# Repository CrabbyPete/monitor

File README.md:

# crib

## Getting started

To make it easy for you to get started with GitLab, here's a list of recommended next steps.

Already a pro? Just edit this README.md and make it your own. Want to make it easy? [Use the template at the bottom](#editing-this-readme)!

## Add your files

- [ ] [Create](https://docs.gitlab.com/ee/user/project/repository/web_editor.html#create-a-file) or [upload](https://docs.gitlab.com/ee/user/project/repository/web_editor.html#upload-a-file) files
- [ ] [Add files using the command line](https://docs.gitlab.com/ee/gitlab-basics/add-file.html#add-a-file-using-the-command-line) or push an existing Git repository with the following command:

```
cd existing_repo
git remote add origin https://gitlab.com/CrabbyPete/crib.git
git branch -M main
git push -uf origin main
```

## Integrate with your tools

- [ ] [Set up project integrations](https://gitlab.com/CrabbyPete/crib/-/settings/integrations)

## Collaborate with your team

- [ ] [Invite team members and collaborators](https://docs.gitlab.com/ee/user/project/members/)
- [ ] [Create a new merge request](https://docs.gitlab.com/ee/user/project/merge_requests/creating_merge_requests.html)
- [ ] [Automatically close issues from merge requests](https://docs.gitlab.com/ee/user/project/issues/managing_issues.html#closing-issues-automatically)
- [ ] [Enable merge request approvals](https://docs.gitlab.com/ee/user/project/merge_requests/approvals/)
- [ ] [Set auto-merge](https://docs.gitlab.com/ee/user/project/merge_requests/merge_when_pipeline_succeeds.html)

## Test and Deploy

Use the built-in continuous integration in GitLab.

- [ ] [Get started with GitLab CI/CD](https://docs.gitlab.com/ee/ci/quick_start/index.html)
- [ ] [Analyze your code for known vulnerabilities with Static Application Security Testing (SAST)](https://docs.gitlab.com/ee/user/application_security/sast/)
- [ ] [Deploy to Kubernetes, Amazon EC2, or Amazon ECS using Auto Deploy](https://docs.gitlab.com/ee/topics/autodevops/requirements.html)
- [ ] [Use pull-based deployments for improved Kubernetes management](https://docs.gitlab.com/ee/user/clusters/agent/)
- [ ] [Set up protected environments](https://docs.gitlab.com/ee/ci/environments/protected_environments.html)

***

# Editing this README

When you're ready to make this README your own, just edit this file and use the handy template below (or feel free to structure it however you want - this is just a starting point!). Thanks to [makeareadme.com](https://www.makeareadme.com/) for this template.

## Suggestions for a good README

Every project is different, so consider which of these sections apply to yours. The sections used in the template are suggestions for most open source projects. Also keep in mind that while a README can be too long and detailed, too long is better than too short. If you think your README is too long, consider utilizing another form of documentation rather than cutting out information.

## Name
Choose a self-explaining name for your project.

## Description
Let people know what your project can do specifically. Provide context and add a link to any reference visitors might be unfamiliar with. A list of Features or a Background subsection can also be added here. If there are alternatives to your project, this is a good place to list differentiating factors.

## Badges
On some READMEs, you may see small images that convey metadata, such as whether or not all the tests are passing for the project. You can use Shields to add some to your README. Many services also have instructions for adding a badge.

## Visuals
Depending on what you are making, it can be a good idea to include screenshots or even a video (you'll frequently see GIFs rather than actual videos). Tools like ttygif can help, but check out Asciinema for a more sophisticated method.

## Installation
Within a particular ecosystem, there may be a common way of installing things, such as using Yarn, NuGet, or Homebrew. However, consider the possibility that whoever is reading your README is a novice and would like more guidance. Listing specific steps helps remove ambiguity and gets people to using your project as quickly as possible. If it only runs in a specific context like a particular programming language version or operating system or has dependencies that have to be installed manually, also add a Requirements subsection.

## Usage
Use examples liberally, and show the expected output if you can. It's helpful to have inline the smallest example of usage that you can demonstrate, while providing links to more sophisticated examples if they are too long to reasonably include in the README.

## Support
Tell people where they can go to for help. It can be any combination of an issue tracker, a chat room, an email address, etc.

## Roadmap
If you have ideas for releases in the future, it is a good idea to list them in the README.

## Contributing
State if you are open to contributions and what your requirements are for accepting them.

For people who want to make changes to your project, it's helpful to have some documentation on how to get started. Perhaps there is a script that they should run or some environment variables that they need to set. Make these steps explicit. These instructions could also be useful to your future self.

You can also document commands to lint the code or run tests. These steps help to ensure high code quality and reduce the likelihood that the changes inadvertently break something. Having instructions for running tests is especially helpful if it requires external setup, such as starting a Selenium server for testing in a browser.

## Authors and acknowledgment
Show your appreciation to those who have contributed to the project.

## License
For open source projects, say how it is licensed.

## Project status
If you have run out of energy or time for your project, put a note at the top of the README saying that development has slowed down or stopped completely. Someone may choose to fork your project or volunteer to step in as a maintainer or owner, allowing your project to keep going. You can also make an explicit request for maintainers.

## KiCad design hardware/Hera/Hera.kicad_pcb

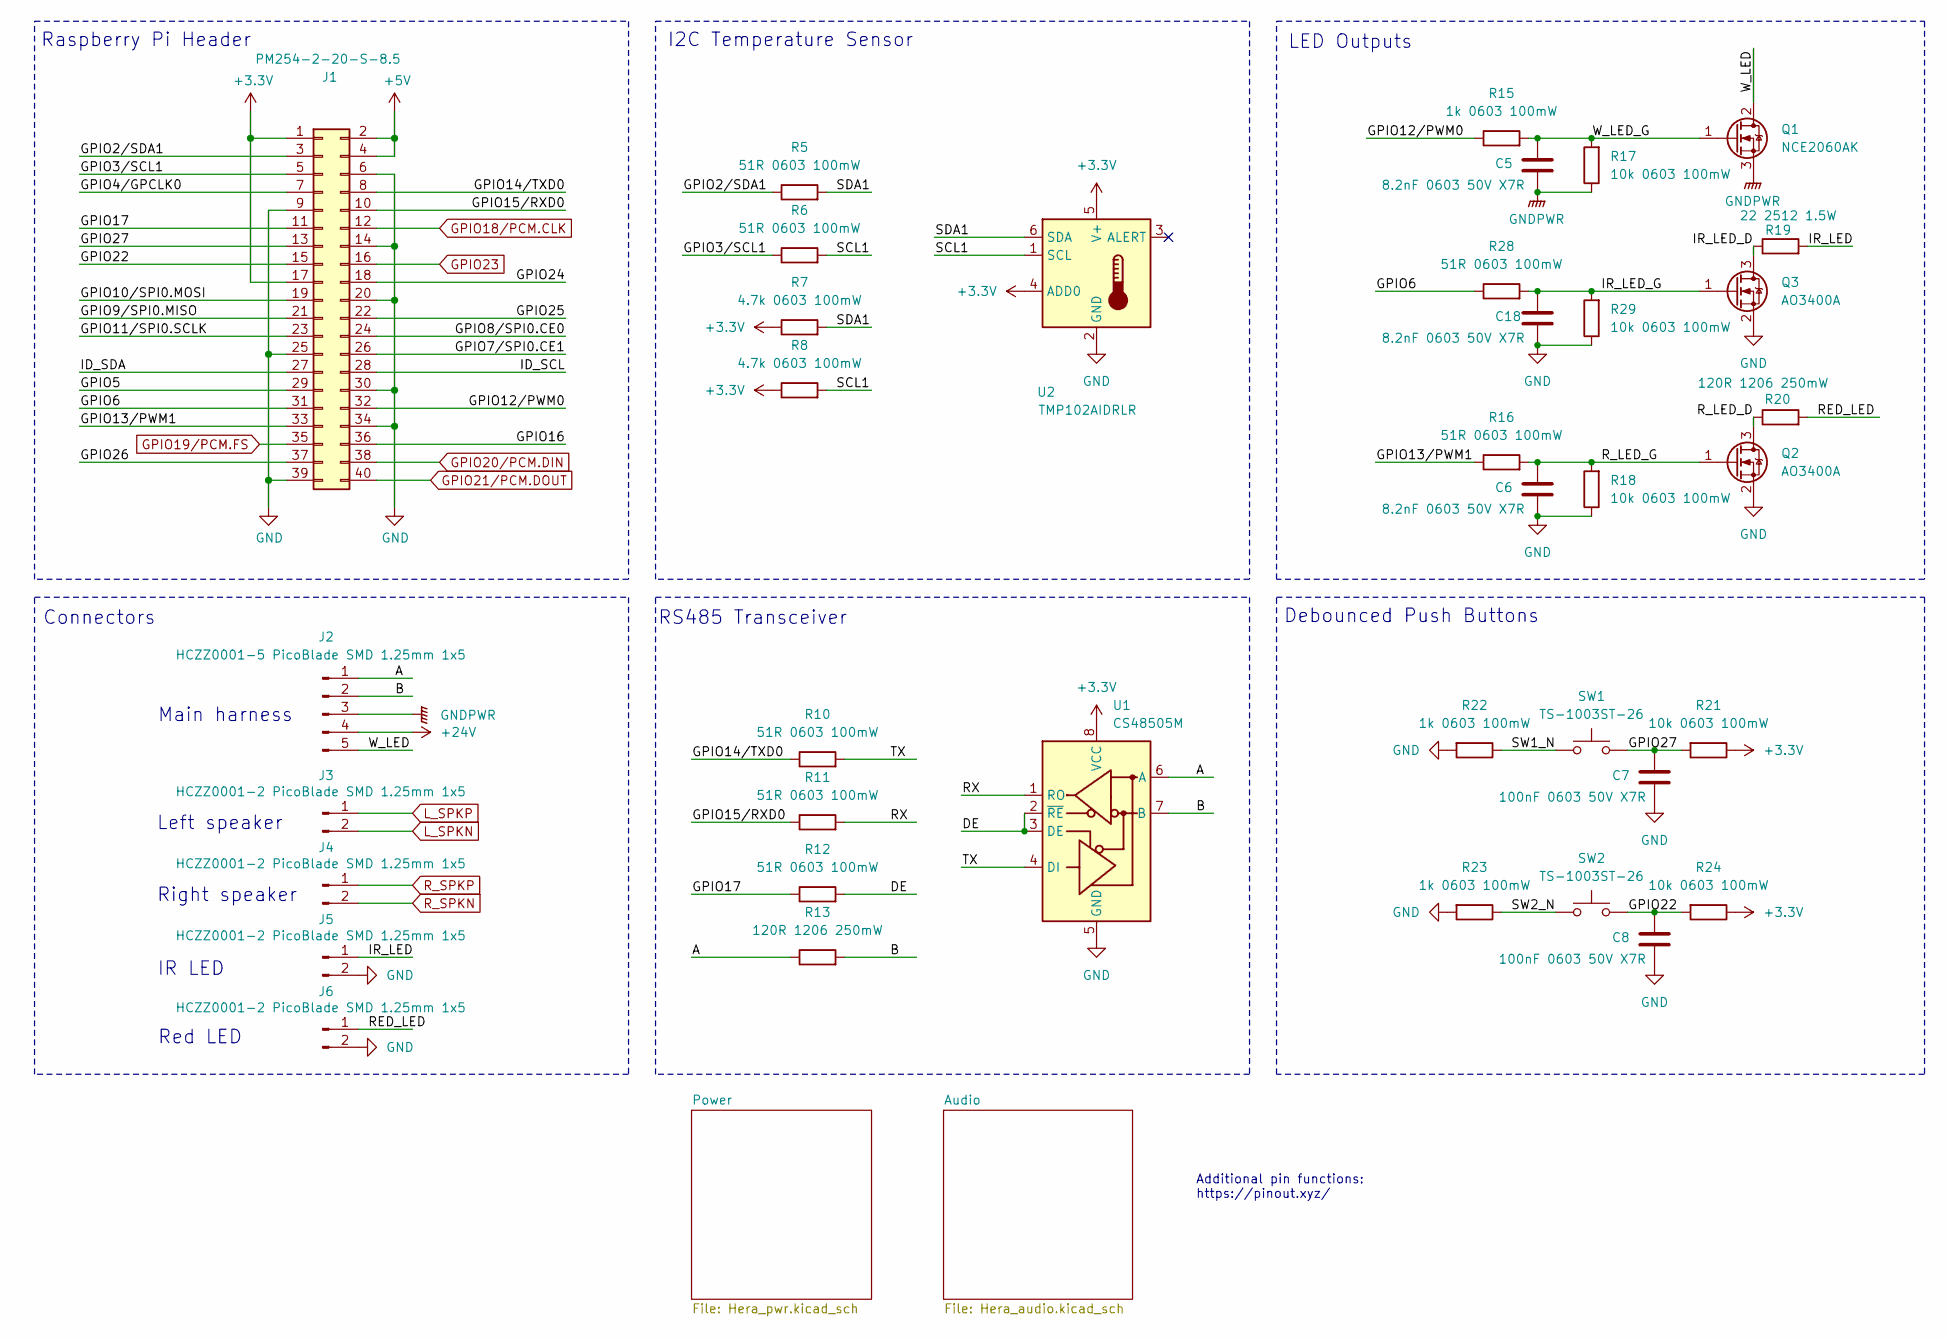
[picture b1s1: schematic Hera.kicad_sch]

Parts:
C5, C6, C18: 8.2nF 0603 50V X7R; C_0603_1608Metric
C7, C8: 100nF 0603 50V X7R; C_0603_1608Metric
J1: PM254-2-20-S-8.5; PinSocket_2x20_P2.54mm_Vertical_SMD
J2: HCZZ0001-5 PicoBlade SMD 1.25mm 1x5; Molex_PicoBlade_53261-0571_1x05-1MP_P1.25mm_Horizontal
J3, J4, J5, J6: HCZZ0001-2 PicoBlade SMD 1.25mm 1x5; Molex_PicoBlade_53261-0271_1x02-1MP_P1.25mm_Horizontal
Q1: NCE2060AK; TO-252-2
Q2, Q3: AO3400A; SOT-23
R5, R6, R10, R11, R12, R16, R28: 51R 0603 100mW; R_0603_1608Metric
R7, R8: 4.7k 0603 100mW; R_0603_1608Metric
R13, R20: 120R 1206 250mW; R_1206_3216Metric
R15, R22, R23: 1k 0603 100mW; R_0603_1608Metric
R17, R18, R21, R24, R29: 10k 0603 100mW; R_0603_1608Metric
R19: 22 2512 1.5W; R_2512_6332Metric
SW1, SW2: TS-1003ST-26; SW_Push_1P1T_NO_CK_PTS125Sx43PSMTR
U1: CS48505M; MSOP-8_3x3mm_P0.65mm
U2: TMP102AIDRLR; SOT-563

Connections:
+3.3V: J1.1, J1.17, R7.1, R8.1, R21.1, R24.1, U1.8 (VCC), U2.4 (ADD0), U2.5 (V+); also elsewhere on the board
+5V: J1.2, J1.4; also elsewhere on the board
+24V: J2.4; also elsewhere on the board
/A: J2.1, R13.1, U1.6 (A)
/B: J2.2, R13.2, U1.7 (B)
/DE: R12.2, U1.2 (~RE), U1.3 (DE)
/GPIO2/SDA1: J1.3, R5.1
/GPIO3/SCL1: J1.5, R6.1
/GPIO4/GPCLK0: J1.7
/GPIO5: J1.29
/GPIO6: J1.31, R28.1
/GPIO7/SPI0.CE1: J1.26
/GPIO8/SPI0.CE0: J1.24
/GPIO9/SPI0.MISO: J1.21
/GPIO10/SPI0.MOSI: J1.19
/GPIO11/SPI0.SCLK: J1.23
/GPIO12/PWM0: J1.32, R15.1
/GPIO13/PWM1: J1.33, R16.1
/GPIO14/TXD0: J1.8, R10.1
/GPIO15/RXD0: J1.10, R11.1
/GPIO16: J1.36
/GPIO17: J1.11, R12.1
/GPIO22: C8.1, J1.15, R24.2, SW2.2
/GPIO24: J1.18
/GPIO25: J1.22
/GPIO26: J1.37
/GPIO27: C7.1, J1.13, R21.2, SW1.2
/ID_SCL: J1.28
/ID_SDA: J1.27
/IR_LED: J5.1, R19.2
/IR_LED_D: Q3.3 (D), R19.1
/IR_LED_G: C18.1, Q3.1 (G), R28.2, R29.2
/RED_LED: J6.1, R20.2
/RX: R11.2, U1.1 (RO)
/R_LED_D: Q2.3 (D), R20.1
/R_LED_G: C6.1, Q2.1 (G), R16.2, R18.2
/SCL1: R6.2, R8.2, U2.1 (SCL)
/SDA1: R5.2, R7.2, U2.6 (SDA)
/SW1_N: R22.1, SW1.1
/SW2_N: R23.1, SW2.1
/TX: R10.2, U1.4 (DI)
/W_LED: J2.5, Q1.2 (D)
/W_LED_G: C5.1, Q1.1 (G), R15.2, R17.2
GND: C6.2, C7.2, C8.2, C18.2, J1.6, J1.9, J1.14, J1.20, J1.25, J1.30, J1.34, J1.39, J5.2, J6.2, Q2.2 (S), Q3.2 (S), R18.1, R22.2, R23.2, R29.1, U1.5 (GND), U2.2 (GND); also elsewhere on the board
GNDPWR: C5.2, J2.3, Q1.3 (S), R17.1; also elsewhere on the board
GPIO18/PCM.CLK: J1.12; also elsewhere on the board
GPIO19/PCM.FS: J1.35; also elsewhere on the board
GPIO20/PCM.DIN: J1.38; also elsewhere on the board
GPIO21/PCM.DOUT: J1.40; also elsewhere on the board
GPIO23: J1.16; also elsewhere on the board
L_SPKN: J3.2; also elsewhere on the board
L_SPKP: J3.1; also elsewhere on the board
R_SPKN: J4.2; also elsewhere on the board
R_SPKP: J4.1; also elsewhere on the board

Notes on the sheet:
Red LED
RS485 Transceiver
Main harness
IR LED
Right speaker
Left speaker
LED Outputs
Raspberry Pi Header
Connectors
I2C Temperature Sensor
Debounced Push Buttons
Additional pin functions: https://pinout.xyz/

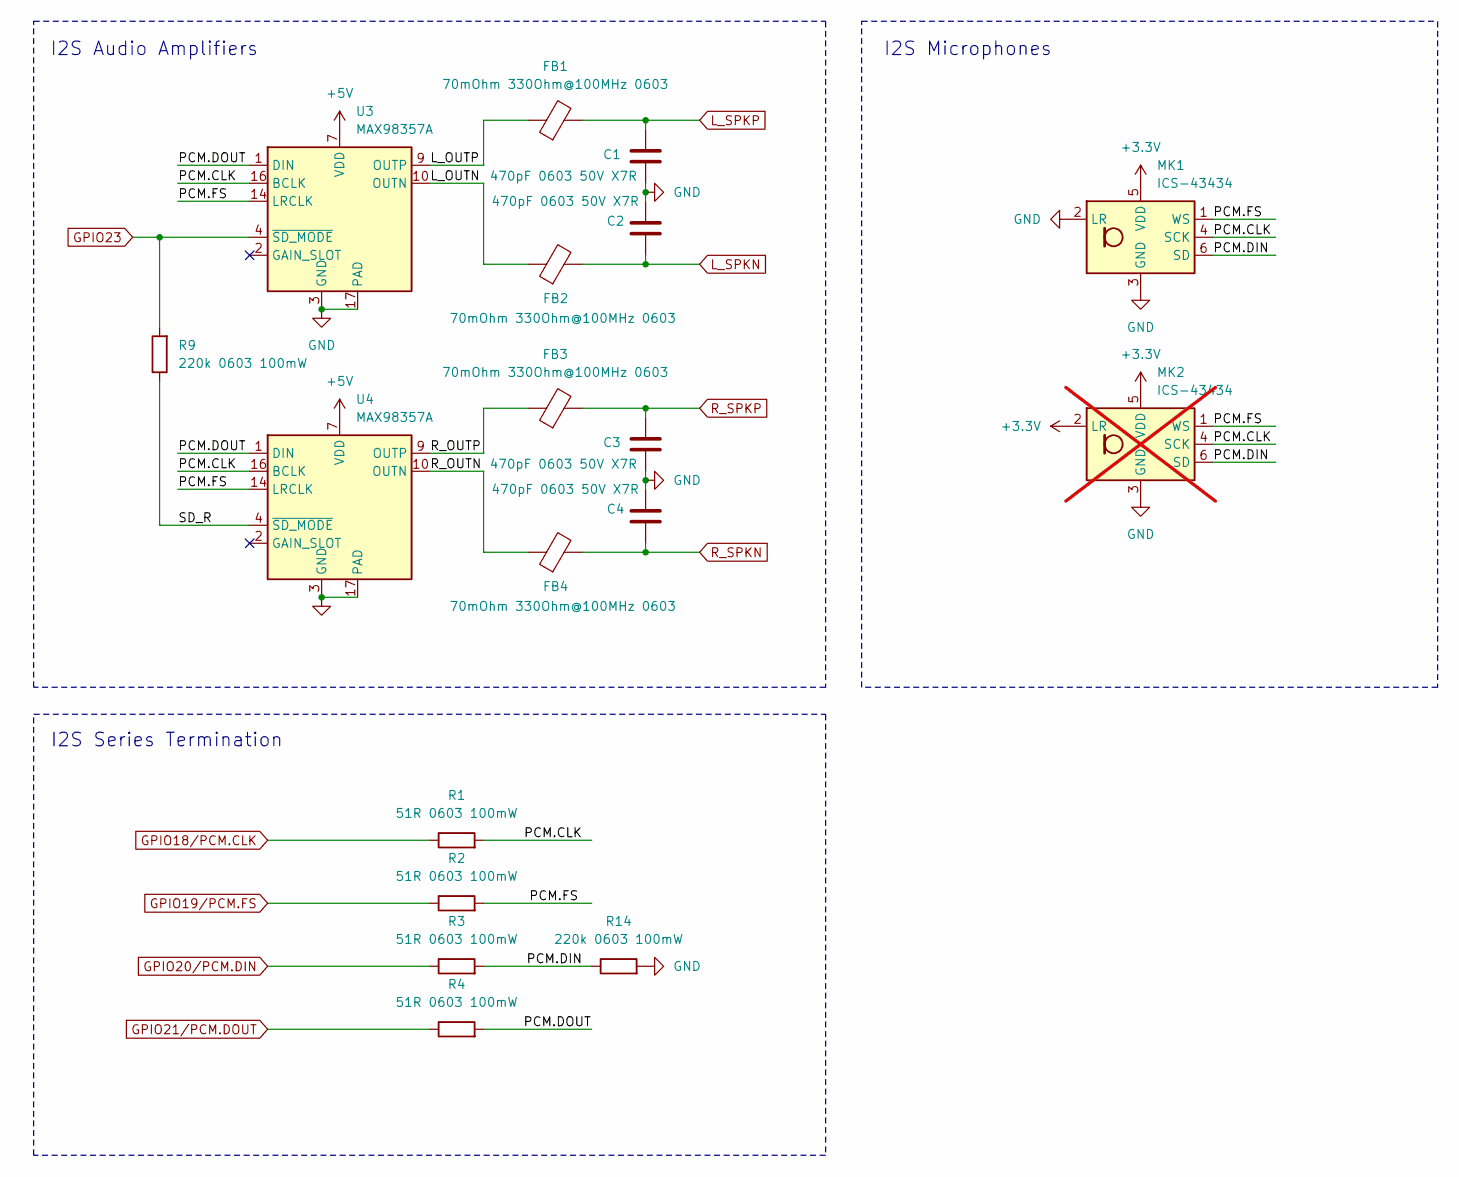
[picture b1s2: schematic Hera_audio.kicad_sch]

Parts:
C1, C2, C3, C4: 470pF 0603 50V X7R; C_0603_1608Metric
FB1, FB2, FB3, FB4: 70mOhm 330Ohm@100MHz 0603; L_0603_1608Metric
MK1: ICS-43434; InvenSense_ICS-43434-6_3.5x2.65mm
MK2: ICS-43434; InvenSense_ICS-43434-6_3.5x2.65mm; not fitted
R1, R2, R3, R4: 51R 0603 100mW; R_0603_1608Metric
R9, R14: 220k 0603 100mW; R_0603_1608Metric
U3, U4: MAX98357A; TQFN-16-1EP_3x3mm_P0.5mm_EP1.23x1.23mm

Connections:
+3.3V: MK1.5 (VDD), MK2.2 (LR), MK2.5 (VDD); also elsewhere on the board
+5V: U3.7 (VDD), U3.8 (VDD), U4.7 (VDD), U4.8 (VDD); also elsewhere on the board
/Audio/L_OUTN: FB2.1, U3.10 (OUTN)
/Audio/L_OUTP: FB1.1, U3.9 (OUTP)
/Audio/PCM.CLK: MK1.4 (SCK), MK2.4 (SCK), R1.2, U3.16 (BCLK), U4.16 (BCLK)
/Audio/PCM.DIN: MK1.6 (SD), MK2.6 (SD), R3.2, R14.1
/Audio/PCM.DOUT: R4.2, U3.1 (DIN), U4.1 (DIN)
/Audio/PCM.FS: MK1.1 (WS), MK2.1 (WS), R2.2, U3.14 (LRCLK), U4.14 (LRCLK)
/Audio/R_OUTN: FB4.1, U4.10 (OUTN)
/Audio/R_OUTP: FB3.1, U4.9 (OUTP)
/Audio/SD_R: R9.1, U4.4 (~SD_MODE)
GND: C1.2, C2.1, C3.2, C4.1, MK1.2 (LR), MK1.3 (GND), MK2.3 (GND), R14.2, U3.3 (GND), U3.11 (GND), U3.15 (GND), U3.17 (PAD), U4.3 (GND), U4.11 (GND), U4.15 (GND), U4.17 (PAD); also elsewhere on the board
GPIO18/PCM.CLK: R1.1; also elsewhere on the board
GPIO19/PCM.FS: R2.1; also elsewhere on the board
GPIO20/PCM.DIN: R3.1; also elsewhere on the board
GPIO21/PCM.DOUT: R4.1; also elsewhere on the board
GPIO23: R9.2, U3.4 (~SD_MODE); also elsewhere on the board
L_SPKN: C2.2, FB2.2; also elsewhere on the board
L_SPKP: C1.1, FB1.2; also elsewhere on the board
R_SPKN: C4.2, FB4.2; also elsewhere on the board
R_SPKP: C3.1, FB3.2; also elsewhere on the board

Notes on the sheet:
I2S Audio Amplifiers
I2S Microphones
I2S Series Termination

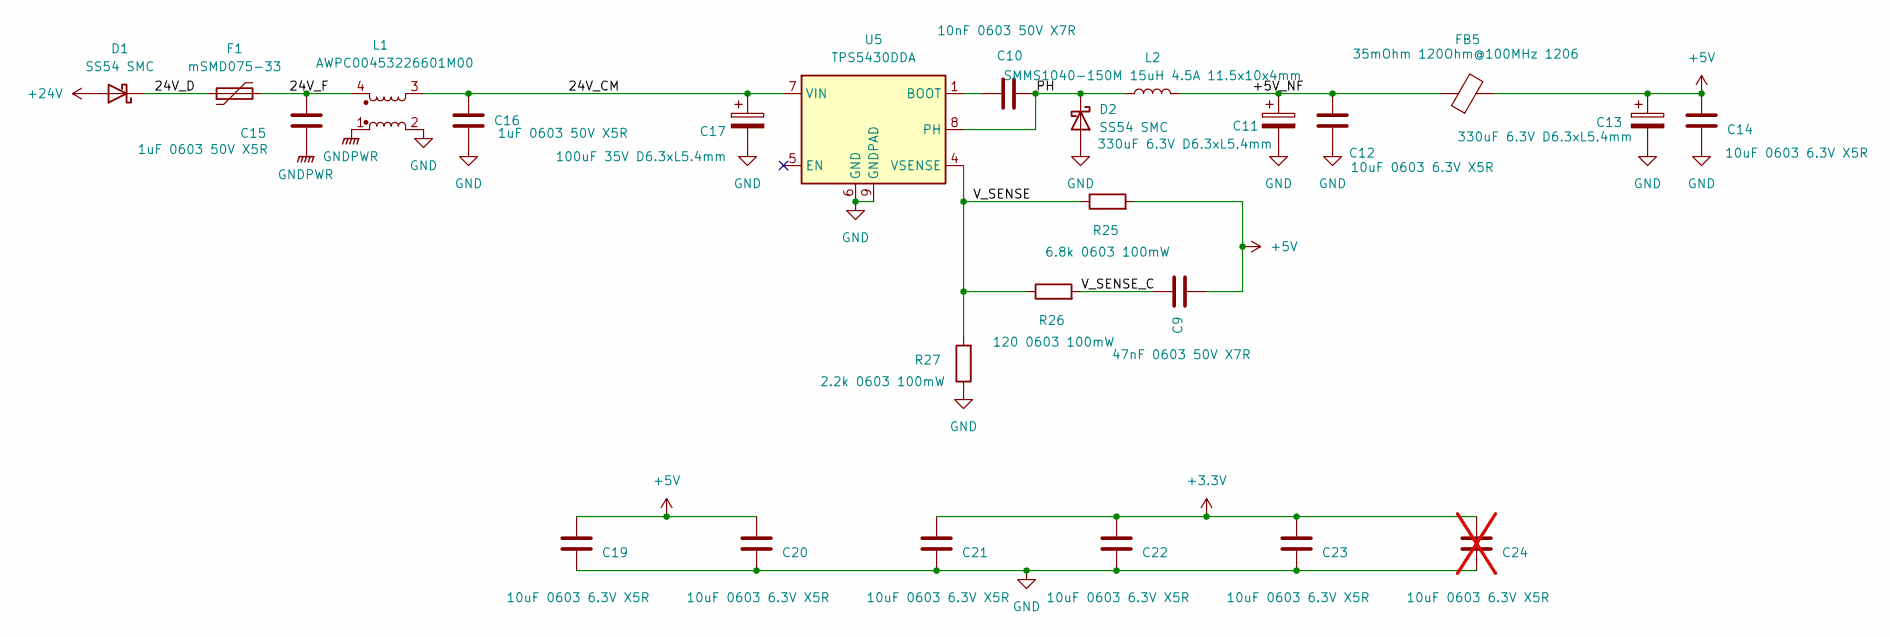
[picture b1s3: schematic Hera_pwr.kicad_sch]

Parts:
C9: 47nF 0603 50V X7R; C_0603_1608Metric
C10: 10nF 0603 50V X7R; C_0603_1608Metric
C11, C13: 330uF 6.3V D6.3xL5.4mm; CP_Elec_6.3x5.4
C12, C14, C19, C20, C21, C22, C23: 10uF 0603 6.3V X5R; C_0603_1608Metric
C15, C16: 1uF 0603 50V X5R; C_0603_1608Metric
C17: 100uF 35V D6.3xL5.4mm; CP_Elec_6.3x5.4
C24: 10uF 0603 6.3V X5R; C_0603_1608Metric; not fitted
D1, D2: SS54 SMC; D_SMC
F1: mSMD075-33; Fuse_1812_4532Metric
FB5: 35mOhm 120Ohm@100MHz 1206; L_1206_3216Metric
L1: AWPC00453226601M00; L_CommonModeChoke_4.5x3.2
L2: SMMS1040-150M 15uH 4.5A 11.5x10x4mm; L_APV_APH1040
R25: 6.8k 0603 100mW; R_0603_1608Metric
R26: 120 0603 100mW; R_0603_1608Metric
R27: 2.2k 0603 100mW; R_0603_1608Metric
U5: TPS5430DDA; TI_SO-PowerPAD-8_ThermalVias

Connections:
+3.3V: C21.2, C22.2, C23.2, C24.2; also elsewhere on the board
+5V: C9.2, C13.1, C14.2, C19.2, C20.2, FB5.2, R25.2; also elsewhere on the board
+24V: D1.2 (A); also elsewhere on the board
/Power/24V_CM: C16.2, C17.1, L1.3, U5.7 (VIN)
/Power/24V_D: D1.1 (K), F1.1
/Power/24V_F: C15.2, F1.2, L1.4
/Power/+5V_NF: C11.1, C12.2, FB5.1, L2.2
/Power/PH: C10.1, D2.1 (K), L2.1, U5.8 (PH)
/Power/V_SENSE: R25.1, R26.1, R27.2, U5.4 (VSENSE)
/Power/V_SENSE_C: C9.1, R26.2
GND: C11.2, C12.1, C13.2, C14.1, C16.1, C17.2, C19.1, C20.1, C21.1, C22.1, C23.1, C24.1, D2.2 (A), L1.2, R27.1, U5.6 (GND), U5.9 (GNDPAD); also elsewhere on the board
GNDPWR: C15.1, L1.1; also elsewhere on the board
unnamed: C10.2, U5.1 (BOOT)

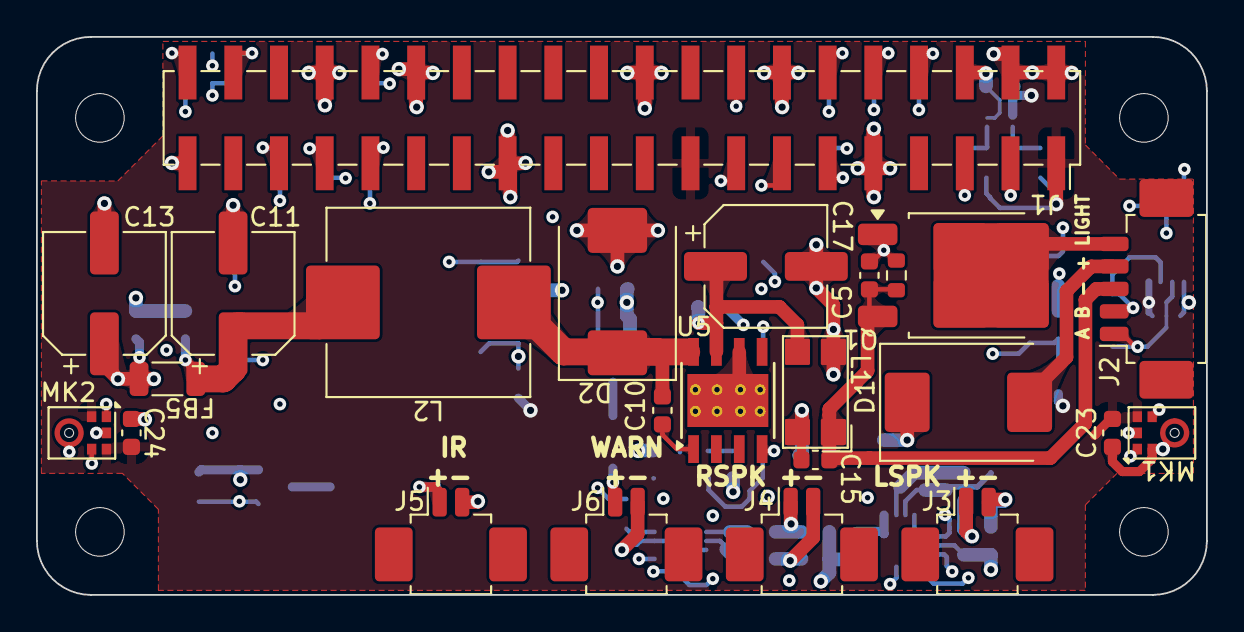
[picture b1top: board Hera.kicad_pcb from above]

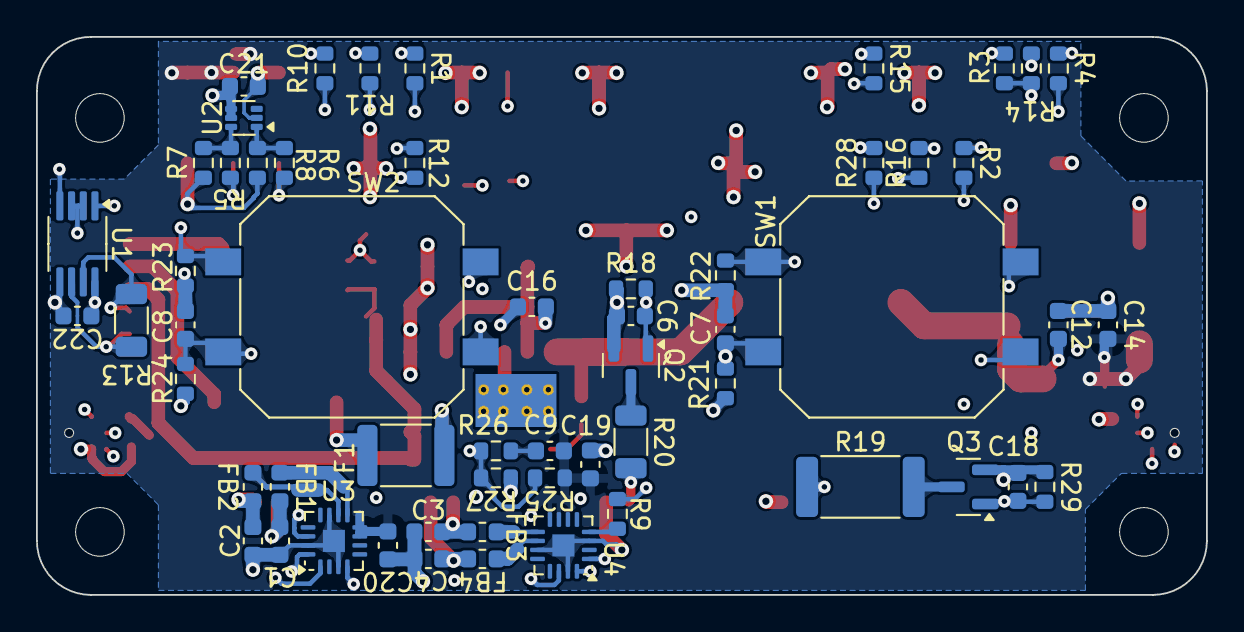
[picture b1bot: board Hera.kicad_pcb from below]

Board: 6 copper layers, 65.0 x 31.0 mm, 85 parts (57 on the bottom side), 58 nets.

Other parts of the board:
MH1, MH2, MH3, MH4: MountingHole_2.7mm_M2.5

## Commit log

2025-01-26 rebase
2025-01-26 Initial push
2025-01-26 turn on lights
2025-02-05 add wav file initialize main and run buttons forever
2025-02-20 change I2c address to 49
2025-03-01 All hardware working
2025-03-14 Code and hardware
